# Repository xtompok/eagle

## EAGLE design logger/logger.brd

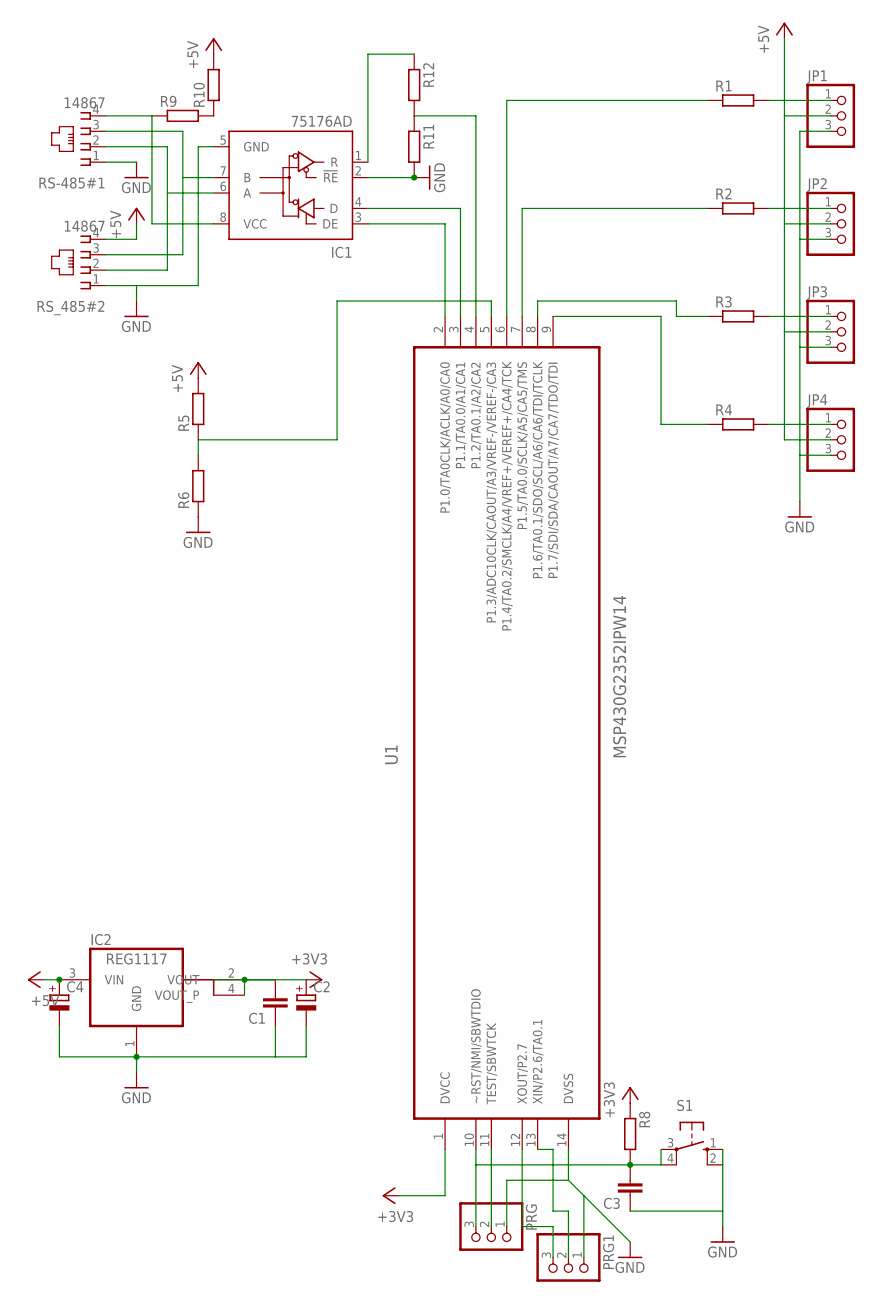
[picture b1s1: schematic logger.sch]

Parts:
C1, C3: C-EUC0805; C0805
C2, C4: CPOL-EUE2,5-6E; E2,5-6E
IC1: 75176AD; D_R-PDSO-G8
IC2: REG1117; SOT223
JP1, JP2, JP3, JP4: PINHD-1X3; 1X03
PRG, PRG1: PINHD-1X3; 1X03
R1, R2, R3, R4, R5, R6, R8, R11, R12: R-EU_R0805; R0805
R9, R10: R-EU_R1206; R1206
RS-485#1: 14867
RS_485#2: 14867
S1: 10-XX; B3F-10XX
U1: MSP430G2352IPW14; SOP65P640X120-14N

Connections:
+3V3: C1.2, C2.+, IC2.2 (VOUT), IC2.4 (VOUT_P), R8.1, U1.1 (DVCC)
+5V: C4.+, IC2.3 (VIN), JP1.2, JP2.2, JP3.2, JP4.2, R5.2, R10.2, RS_485#2.4
GND: C1.1, C2.-, C3.1, C4.-, IC1.2 (!RE), IC1.5 (GND), IC2.1 (GND), JP1.3, JP2.3, JP3.3, JP4.3, PRG.1, PRG1.1, R6.1, R11.2, RS-485#1.1, RS_485#2.1, S1.1 (S), S1.2 (S1), U1.14 (DVSS)
unnamed: IC1.6 (A), RS-485#1.2, RS_485#2.2
unnamed: IC1.7 (B), RS-485#1.3, RS_485#2.3
unnamed: R5.1, R6.2, U1.5 (P1.3/ADC10CLK/CAOUT/A3/VREF-/VEREF-/CA3)
unnamed: R4.1, U1.9 (P1.7/SDI/SDA/CAOUT/A7/CA7/TDO/TDI)
unnamed: JP4.1, R4.2
unnamed: JP3.1, R3.2
unnamed: JP2.1, R2.2
unnamed: JP1.1, R1.2
unnamed: R3.1, U1.8 (P1.6/TA0.1/SDO/SCL/A6/CA6/TDI/TCLK)
unnamed: R2.1, U1.7 (P1.5/TA0.0/SCLK/A5/CA5/TMS)
unnamed: R1.1, U1.6 (P1.4/TA0.2/SMCLK/A4/VREF+/VEREF+/CA4/TCK)
unnamed: PRG1.2, U1.13 (XIN/P2.6/TA0.1)
unnamed: IC1.4 (D), U1.3 (P1.1/TA0.0/A1/CA1)
unnamed: IC1.3 (DE), U1.2 (P1.0/TA0CLK/ACLK/A0/CA0)
unnamed: C3.2, PRG.3, R8.2, S1.3, S1.4 (P1), U1.10 (~RST/NMI/SBWTDIO)
unnamed: PRG.2, U1.11 (TEST/SBWTCK)
unnamed: PRG1.3, U1.12 (XOUT/P2.7)
unnamed: R9.2, R10.1
unnamed: IC1.8 (VCC), R9.1, RS-485#1.4
unnamed: IC1.1 (R), R12.1
unnamed: R11.1, R12.2, U1.4 (P1.2/TA0.1/A2/CA2)

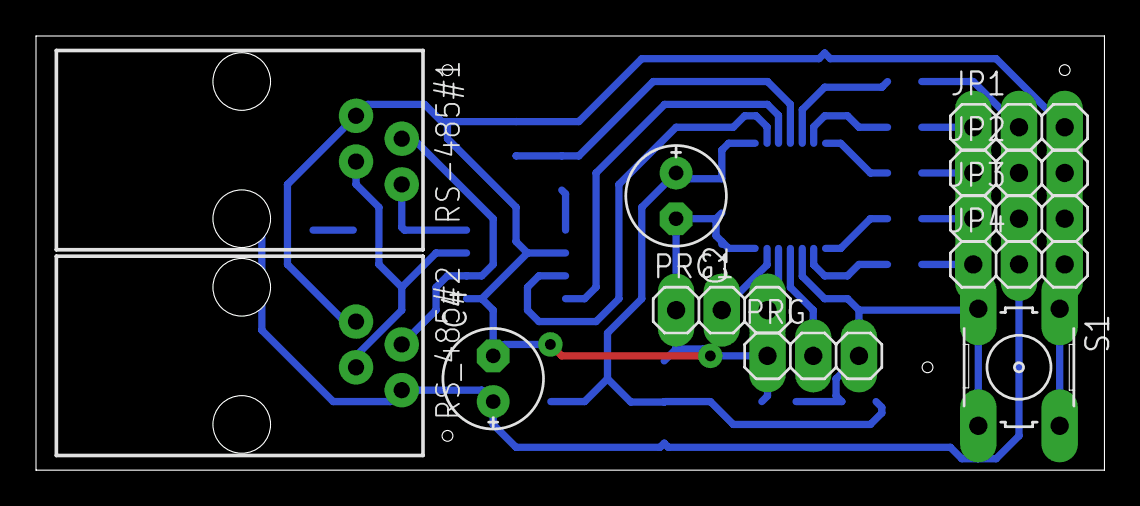
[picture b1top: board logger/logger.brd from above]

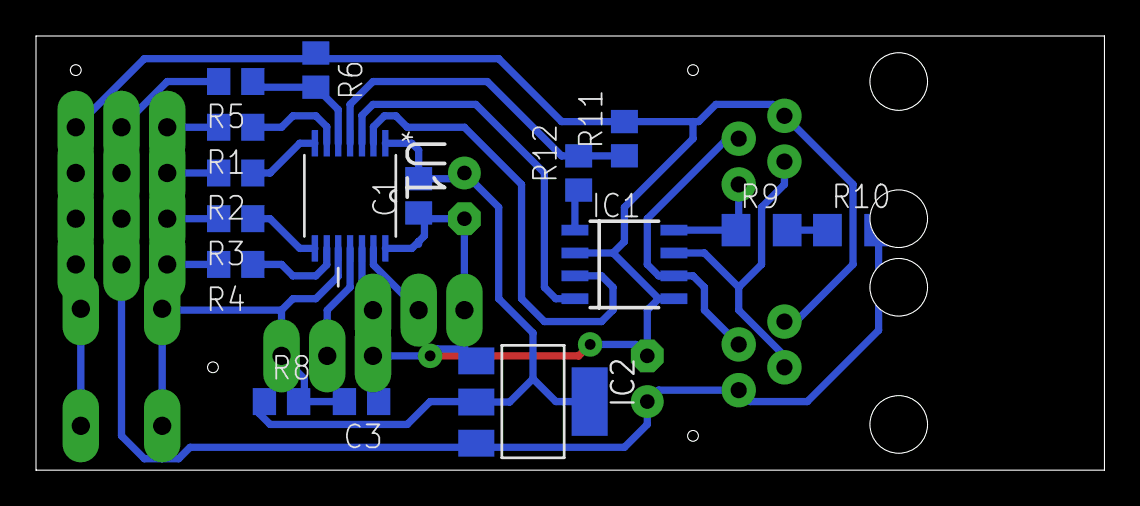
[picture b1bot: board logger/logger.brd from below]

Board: 2 copper layers, 59.4 x 24.1 mm, 27 parts (16 on the bottom side), 24 nets.

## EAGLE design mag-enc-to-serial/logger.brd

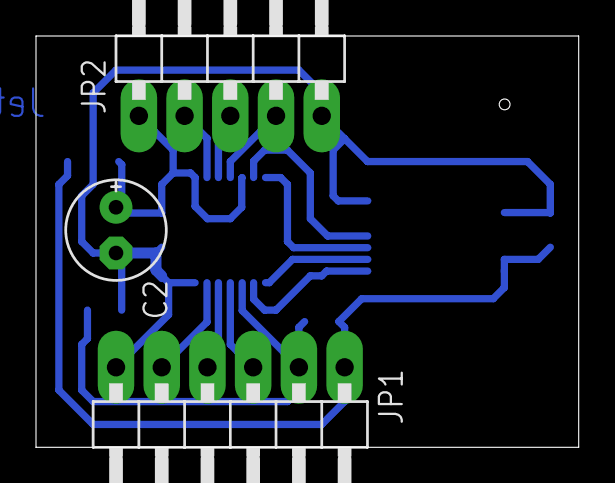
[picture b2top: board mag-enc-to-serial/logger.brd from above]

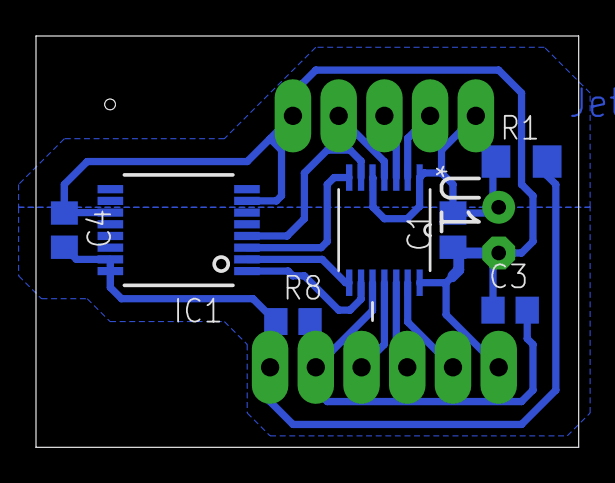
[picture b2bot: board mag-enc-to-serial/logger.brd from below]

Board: 2 copper layers, 30.2 x 22.9 mm, 10 parts (7 on the bottom side), 14 nets.

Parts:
C1, C3, C4: C0805
C2: E2,5-6E
IC1: AS5040; SSOP16
JP1: 1X06/90
JP2: 1X05/90
R1: R1206
R8: R0805
U1: MSP430G2352IPW14; SOP65P640X120-14N

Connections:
+3V3: C1.2, C2.+, JP2.1, R1.1, U1.1, U1.5
GND: C1.1, C2.-, C3.1, C4.1, IC1.7, IC1.11, JP1.6, JP2.5, U1.14
unnamed: JP1.3, U1.11
unnamed: JP2.3, U1.3
unnamed: JP1.4, U1.12
unnamed: IC1.4, U1.6
unnamed: IC1.3, U1.7
unnamed: C4.2, IC1.15, IC1.16, JP1.1, R1.2, R8.1
unnamed: JP1.5, U1.13
unnamed: IC1.2, U1.8
unnamed: IC1.1, U1.9
unnamed: JP2.2, U1.2
unnamed: C3.2, JP1.2, R8.2, U1.10
unnamed: JP2.4, U1.4

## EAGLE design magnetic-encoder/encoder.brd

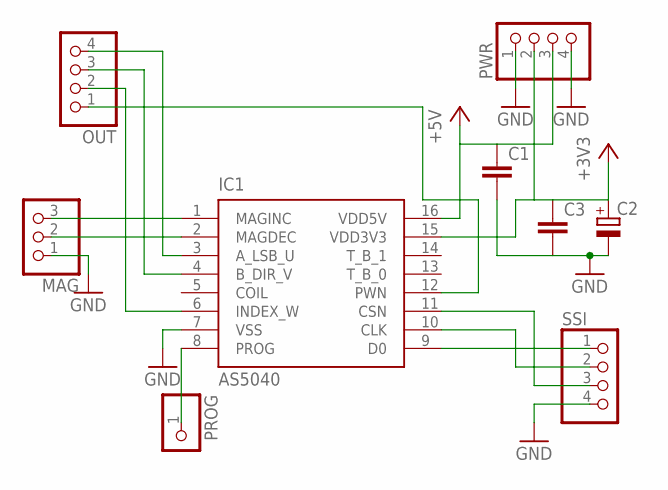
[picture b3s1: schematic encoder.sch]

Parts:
C1, C3: C-EUC0805; C0805
C2: CPOL-EUE2,5-6E; E2,5-6E
IC1: AS5040; SSOP16
MAG: PINHD-1X3; 1X03
OUT: PINHD-1X4; 1X04
PROG: PINHD-1X1; 1X01
PWR: PINHD-1X4; 1X04
SSI: PINHD-1X4; 1X04

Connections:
+3V3: C2.+, C3.1, IC1.15 (VDD3V3), PWR.2
+5V: C1.1, IC1.16 (VDD5V), PWR.3
GND: C1.2, C2.-, C3.2, IC1.7 (VSS), MAG.1, PWR.1, PWR.4, SSI.4
unnamed: IC1.11 (CSN), SSI.3
unnamed: IC1.3 (A_LSB_U), OUT.4
unnamed: IC1.4 (B_DIR_V), OUT.3
unnamed: IC1.6 (INDEX_W), OUT.2
unnamed: IC1.12 (PWN), OUT.1
unnamed: IC1.2 (MAGDEC), MAG.2
unnamed: IC1.1 (MAGINC), MAG.3
unnamed: IC1.10 (CLK), SSI.2
unnamed: IC1.9 (D0), SSI.1
unnamed: IC1.8 (PROG), PROG.1

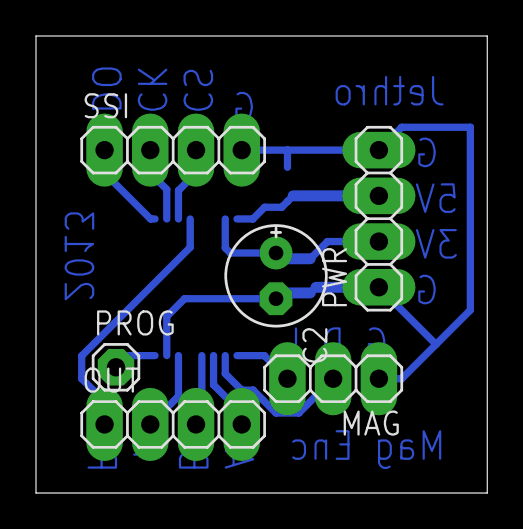
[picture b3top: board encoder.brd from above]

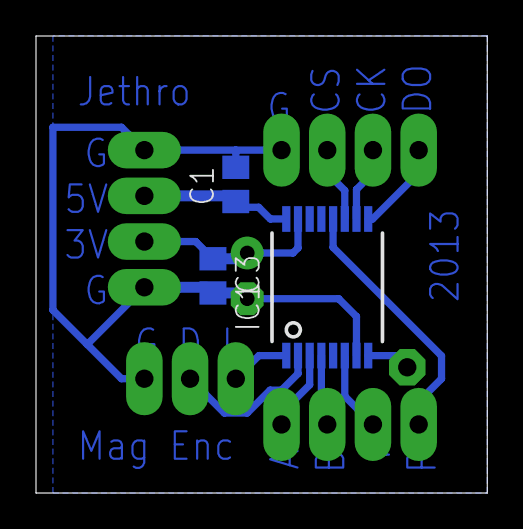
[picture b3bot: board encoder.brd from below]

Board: 2 copper layers, 25.1 x 25.4 mm, 9 parts (3 on the bottom side), 13 nets.
